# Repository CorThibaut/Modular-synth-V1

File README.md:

# Modular-synth-V1
Personal project focused on building multiple analog synthesizer modules for the Eurorack format.

## Gallery

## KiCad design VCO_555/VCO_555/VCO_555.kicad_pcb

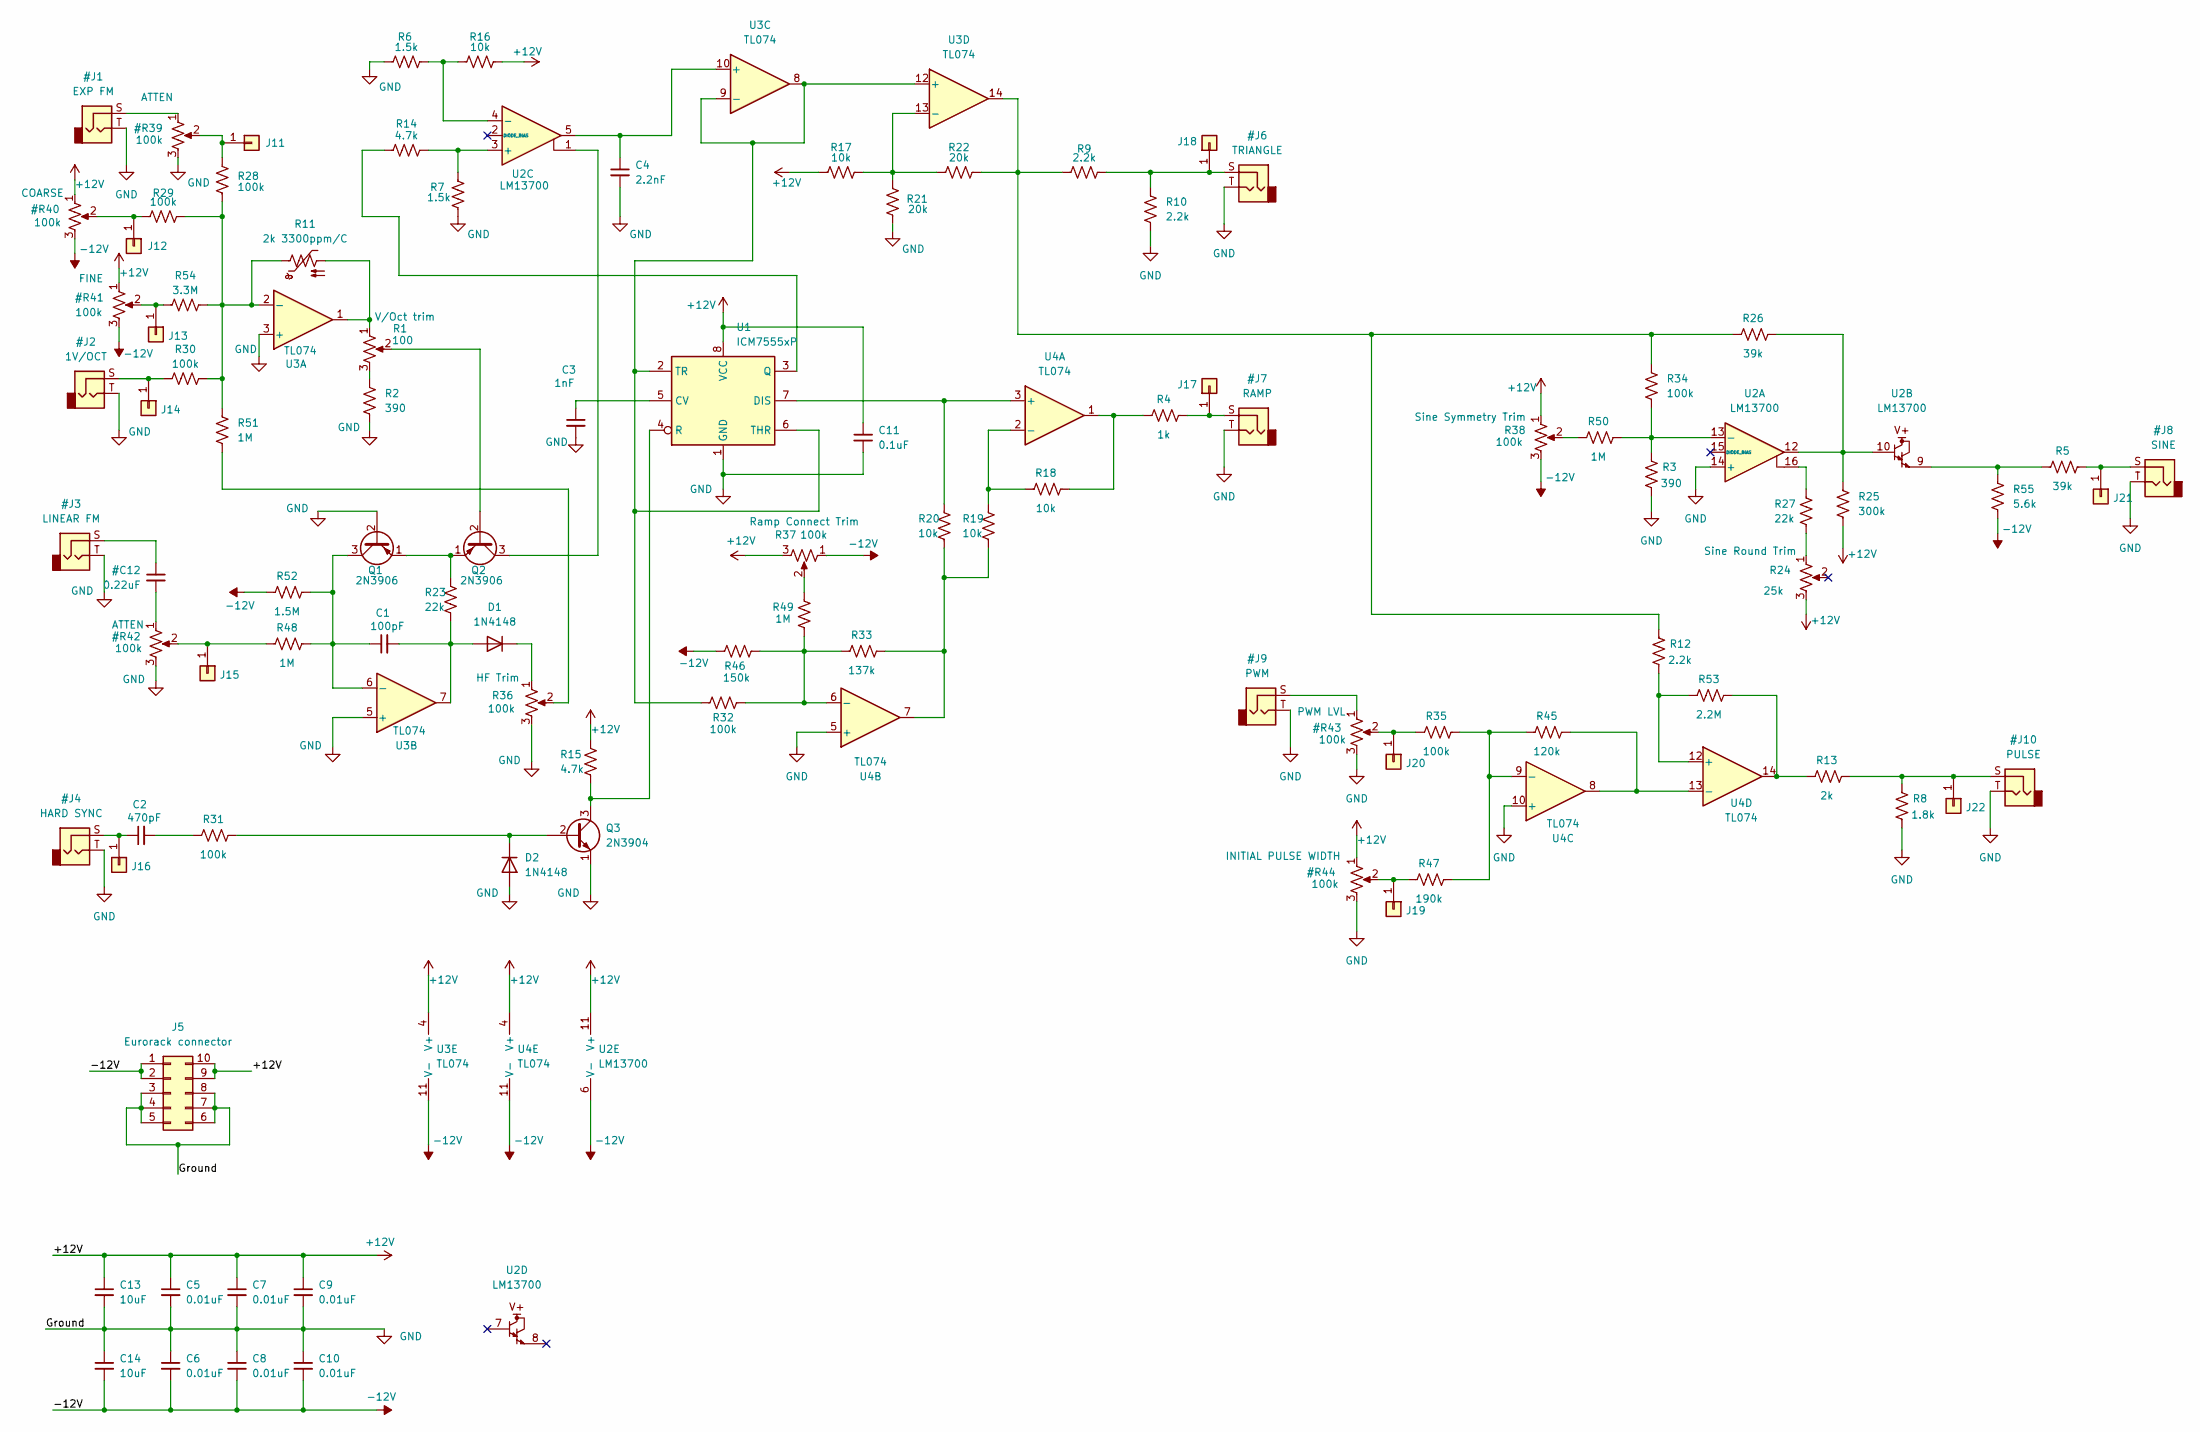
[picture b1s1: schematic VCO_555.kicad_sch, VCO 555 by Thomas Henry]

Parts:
C1: 100pF; C_Axial_L3.8mm_D2.6mm_P7.50mm_Horizontal
C2: 470pF; C_Disc_D7.5mm_W2.5mm_P5.00mm
C3: 1nF; C_Disc_D4.7mm_W2.5mm_P5.00mm
C4: 2.2nF; C_Disc_D5.1mm_W3.2mm_P5.00mm
C5, C6, C7, C8, C9, C10: 0.01uF; C_Disc_D5.0mm_W2.5mm_P5.00mm
C11: 0.1uF; C_Rect_L4.6mm_W3.0mm_P2.50mm_MKS02_FKP02
C13, C14: 10uF; CP_Radial_Tantal_D10.5mm_P5.00mm
D1, D2: 1N4148; D_DO-35_SOD27_P7.62mm_Horizontal
J5: Eurorack connector; IDC-Header_2x05_P2.54mm_Vertical
J11: EXP FM; Pin_D0.7mm_L6.5mm_W1.8mm_FlatFork
J12: COARSE; Pin_D0.7mm_L6.5mm_W1.8mm_FlatFork
J13: FINE; Pin_D0.7mm_L6.5mm_W1.8mm_FlatFork
J14: 1V/OCT; Pin_D0.7mm_L6.5mm_W1.8mm_FlatFork
J15: Linear FM; Pin_D0.7mm_L6.5mm_W1.8mm_FlatFork
J16: HardSync; Pin_D0.7mm_L6.5mm_W1.8mm_FlatFork
J17: Conn_01x01; Pin_D0.7mm_L6.5mm_W1.8mm_FlatFork
J18: Triangle; Pin_D0.7mm_L6.5mm_W1.8mm_FlatFork
J19: INIT PW; Pin_D0.7mm_L6.5mm_W1.8mm_FlatFork
J20: PWM; Pin_D0.7mm_L6.5mm_W1.8mm_FlatFork
J21: Sine; Pin_D0.7mm_L6.5mm_W1.8mm_FlatFork
J22: Pulse; Pin_D0.7mm_L6.5mm_W1.8mm_FlatFork
Q1, Q2: 2N3906; TO-92_Inline
Q3: 2N3904; TO-92_Inline
R1: 100; Potentiometer_Bourns_3386X_Horizontal
R2, R3: 390; R_Axial_DIN0207_L6.3mm_D2.5mm_P10.16mm_Horizontal
R4: 1k; R_Axial_DIN0207_L6.3mm_D2.5mm_P10.16mm_Horizontal
R5, R26: 39k; R_Axial_DIN0207_L6.3mm_D2.5mm_P10.16mm_Horizontal
R6, R7: 1.5k; R_Axial_DIN0207_L6.3mm_D2.5mm_P10.16mm_Horizontal
R8: 1.8k; R_Axial_DIN0207_L6.3mm_D2.5mm_P10.16mm_Horizontal
R9, R10, R12: 2.2k; R_Axial_DIN0207_L6.3mm_D2.5mm_P10.16mm_Horizontal
R11: 2k 3300ppm/C; R_Axial_DIN0207_L6.3mm_D2.5mm_P7.62mm_Horizontal
R13: 2k; R_Axial_DIN0207_L6.3mm_D2.5mm_P10.16mm_Horizontal
R14, R15: 4.7k; R_Axial_DIN0207_L6.3mm_D2.5mm_P10.16mm_Horizontal
R16, R17, R18, R19, R20: 10k; R_Axial_DIN0207_L6.3mm_D2.5mm_P10.16mm_Horizontal
R21, R22: 20k; R_Axial_DIN0207_L6.3mm_D2.5mm_P10.16mm_Horizontal
R23, R27: 22k; R_Axial_DIN0207_L6.3mm_D2.5mm_P10.16mm_Horizontal
R24: 25k; Potentiometer_Bourns_3296W_Vertical
R25: 300k; R_Axial_DIN0207_L6.3mm_D2.5mm_P10.16mm_Horizontal
R28, R29, R30, R31, R32, R34, R35: 100k; R_Axial_DIN0207_L6.3mm_D2.5mm_P10.16mm_Horizontal
R33: 137k; R_Axial_DIN0207_L6.3mm_D2.5mm_P10.16mm_Horizontal
R36: 100k; Potentiometer_Piher_PT-6-V_Vertical
R37: 100k; Potentiometer_Bourns_3296W_Vertical
R38: 100k; Potentiometer_Bourns_3296Y_Vertical
R45: 120k; R_Axial_DIN0207_L6.3mm_D2.5mm_P10.16mm_Horizontal
R46: 150k; R_Axial_DIN0207_L6.3mm_D2.5mm_P10.16mm_Horizontal
R47: 190k; R_Axial_DIN0207_L6.3mm_D2.5mm_P10.16mm_Horizontal
R48, R49, R50, R51: 1M; R_Axial_DIN0207_L6.3mm_D2.5mm_P10.16mm_Horizontal
R52: 1.5M; R_Axial_DIN0207_L6.3mm_D2.5mm_P10.16mm_Horizontal
R53: 2.2M; R_Axial_DIN0207_L6.3mm_D2.5mm_P10.16mm_Horizontal
R54: 3.3M; R_Axial_DIN0207_L6.3mm_D2.5mm_P10.16mm_Horizontal
R55: 5.6k; R_Axial_DIN0207_L6.3mm_D2.5mm_P10.16mm_Horizontal
U1: ICM7555xP; CERDIP-8_W7.62mm_SideBrazed_Socket
U2: LM13700; CERDIP-16_W7.62mm_SideBrazed_Socket
U3, U4: TL074; CERDIP-14_W7.62mm_SideBrazed_Socket

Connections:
unnamed: C2.2, R31.1
unnamed: C1.2, D1.2 (A), R23.2, U3.7
unnamed: D1.1 (K), R36.1
unnamed: D2.1 (K), Q3.2 (B), R31.2
unnamed: C1.1, Q1.3 (C), R48.2, R52.2, U3.6 (-)
unnamed: Q1.1 (E), Q2.1 (E), R23.1
unnamed: Q2.2 (B), R1.2
unnamed: Q2.3 (C), U2.1
unnamed: Q3.3 (C), R15.2, U1.4 (R)
unnamed: R1.1, R11.2, U3.1
unnamed: R1.3, R2.1
unnamed: R5.1, R55.1, U2.9
unnamed: R9.1, R12.1, R22.2, R26.1, R34.1, U3.14
unnamed: R13.1, R53.2, U4.14
unnamed: R4.1, R18.2, U4.1
unnamed: R19.2, R20.2, R33.2, U4.7
unnamed: R24.1, R27.2
unnamed: R25.1, R26.2, U2.10, U2.12
unnamed: R27.1, U2.16
unnamed: R36.2, R51.2
unnamed: R37.2, R49.1
unnamed: R38.2, R50.1
unnamed: C3.1, U1.5 (CV)
unnamed: R20.1, U1.7 (DIS), U4.3 (+)
unnamed: R14.1, U1.3 (Q)
unnamed: R32.1, U1.2 (TR), U1.6 (THR), U3.8, U3.9 (-), U3.12 (+)
unnamed: R3.1, R34.2, R50.2, U2.13 (-)
unnamed: R7.2, R14.2, U2.3 (+)
unnamed: R6.2, R16.1, U2.4 (-)
unnamed: R11.1, R28.2, R29.2, R30.2, R51.1, R54.2, U3.2 (-)
unnamed: C4.1, U2.5, U3.10 (+)
unnamed: R17.2, R21.1, R22.1, U3.13 (-)
unnamed: R18.1, R19.1, U4.2 (-)
unnamed: R32.2, R33.1, R46.2, R49.2, U4.6 (-)
unnamed: R35.2, R45.1, R47.2, U4.9 (-)
unnamed: R12.2, R53.1, U4.12 (+)
unnamed: R45.2, U4.8, U4.13 (-)

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
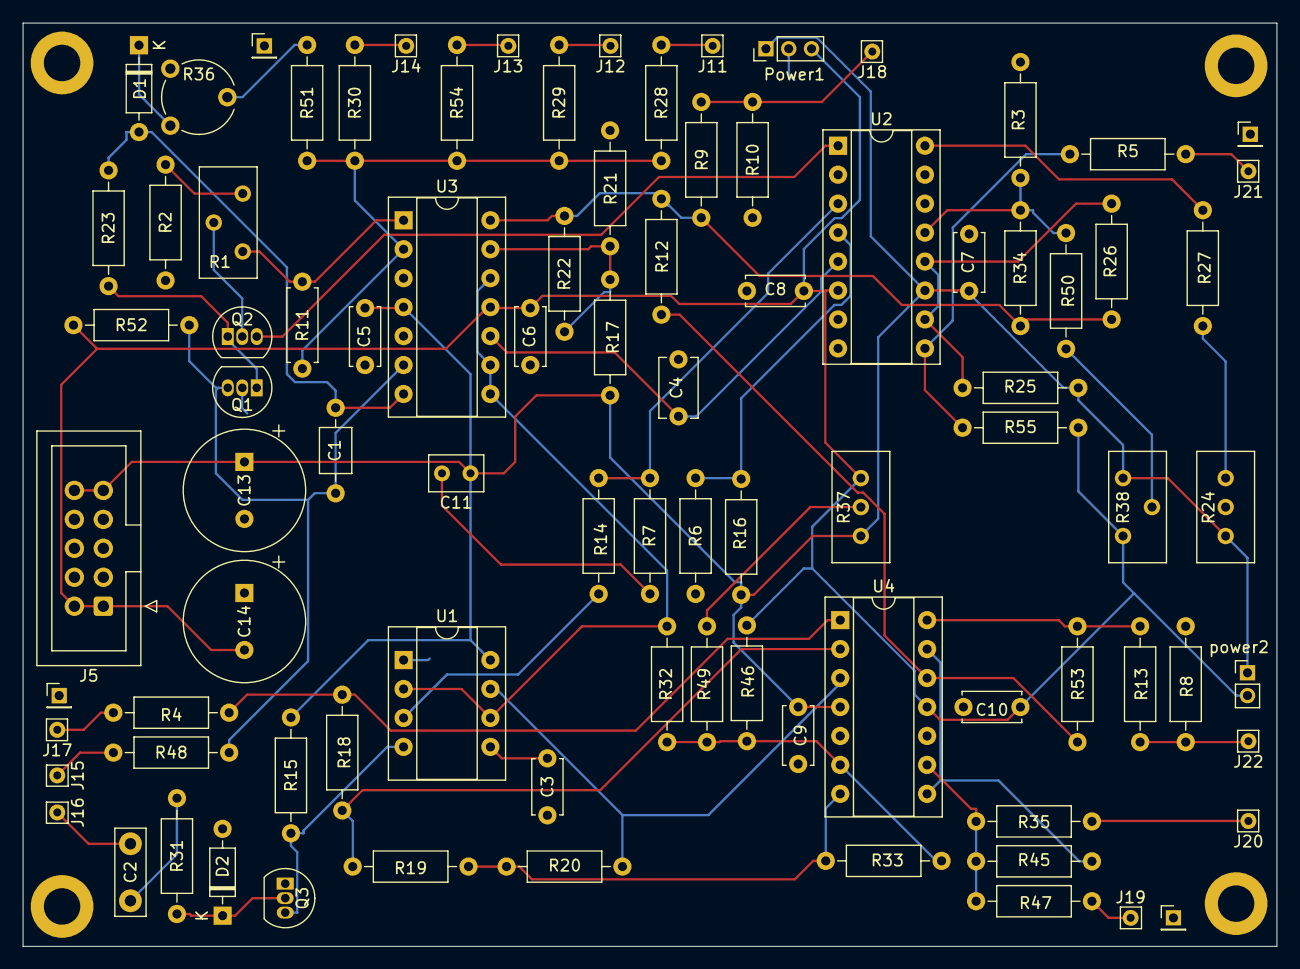
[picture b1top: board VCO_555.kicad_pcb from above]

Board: 2 copper layers, 110.0 x 81.0 mm, 94 parts (0 on the bottom side), 52 nets.

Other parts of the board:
GND1, GND2, GND3, GND4: PinHeader_1x01_P2.00mm_Vertical
MH1, MH2, MH3, MH4: MountingHole_3.2mm_M3_ISO14580_Pad
Power1: PinHeader_1x03_P2.00mm_Vertical
power2: PinHeader_1x02_P2.00mm_Vertical

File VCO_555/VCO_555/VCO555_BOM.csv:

"Reference","Value","Datasheet","Footprint","Qty","DNP"
"C1","100pF","~","","1",""
"C2","470pF","~","","1",""
"C3","0.001uF","~","","1",""
"C4","2200pF","~","","1",""
"C5,C6,C7,C8,C9,C10","0.01uF","~","","6",""
"C11","0.1uF","~","","1",""
"C12","0.22uF","~","","1",""
"C13,C14","10uF","~","","2",""
"D1,D2","1N4148","https://assets.nexperia.com/documents/data-sheet/1N4148_1N4448.pdf","Diode_THT:D_DO-35_SOD27_P7.62mm_Horizontal","2",""
"J1","EXP FM","~","Connector_Audio:Jack_3.5mm_CUI_SJ1-3523N_Horizontal","1",""
"J2","1V/OCT","~","Connector_Audio:Jack_3.5mm_CUI_SJ1-3523N_Horizontal","1",""
"J3","LINEAR FM","~","Connector_Audio:Jack_3.5mm_CUI_SJ1-3523N_Horizontal","1",""
"J4","HARD SYNC","~","Connector_Audio:Jack_3.5mm_CUI_SJ1-3523N_Horizontal","1",""
"J5","Eurorack connector","~","Connector_Harwin:Harwin_Gecko-G125-MVX1605L0X_2x08_P1.25mm_Vertical","1",""
"J6","TRIANGLE","~","Connector_Audio:Jack_3.5mm_CUI_SJ1-3523N_Horizontal","1",""
"J7","RAMP","~","Connector_Audio:Jack_3.5mm_CUI_SJ1-3523N_Horizontal","1",""
"J8","SINE","~","Connector_Audio:Jack_3.5mm_CUI_SJ1-3523N_Horizontal","1",""
"J9","PWM","~","Connector_Audio:Jack_3.5mm_CUI_SJ1-3523N_Horizontal","1",""
"J10","PULSE","~","Connector_Audio:Jack_3.5mm_CUI_SJ1-3523N_Horizontal","1",""
"Q1,Q2","2N3906","https://www.onsemi.com/pub/Collateral/2N3906-D.PDF","Package_TO_SOT_THT:TO-92_Inline","2",""
"Q3","2N3904","https://www.onsemi.com/pub/Collateral/2N3903-D.PDF","Package_TO_SOT_THT:TO-92_Inline","1",""
"R1","100","~","Potentiometer_SMD:Potentiometer_ACP_CA6-VSMD_Vertical","1",""
"R2,R3","390","~","Resistor_THT:R_Axial_DIN0207_L6.3mm_D2.5mm_P10.16mm_Horizontal","2",""
"R4","1k","~","Resistor_THT:R_Axial_DIN0207_L6.3mm_D2.5mm_P10.16mm_Horizontal","1",""
"R5,R26","39k","~","Resistor_THT:R_Axial_DIN0207_L6.3mm_D2.5mm_P10.16mm_Horizontal","2",""
"R6,R7","1.5k","~","Resistor_THT:R_Axial_DIN0207_L6.3mm_D2.5mm_P10.16mm_Horizontal","2",""
"R8","1.8k","~","Resistor_THT:R_Axial_DIN0207_L6.3mm_D2.5mm_P10.16mm_Horizontal","1",""
"R9,R10,R12","2.2k","~","Resistor_THT:R_Axial_DIN0207_L6.3mm_D2.5mm_P10.16mm_Horizontal","3",""
"R11","2k 3300ppm/C","~","Resistor_THT:R_Axial_DIN0207_L6.3mm_D2.5mm_P7.62mm_Horizontal","1",""
"R13","2k","~","Resistor_THT:R_Axial_DIN0207_L6.3mm_D2.5mm_P10.16mm_Horizontal","1",""
"R14,R15","4.7k","~","Resistor_THT:R_Axial_DIN0207_L6.3mm_D2.5mm_P10.16mm_Horizontal","2",""
"R16,R17,R18,R19,R20","10k","~","Resistor_THT:R_Axial_DIN0207_L6.3mm_D2.5mm_P10.16mm_Horizontal","5",""
"R21,R22","20k","~","Resistor_THT:R_Axial_DIN0207_L6.3mm_D2.5mm_P10.16mm_Horizontal","2",""
"R23,R27","22k","~","Resistor_THT:R_Axial_DIN0207_L6.3mm_D2.5mm_P10.16mm_Horizontal","2",""
"R24","25k","~","Potentiometer_SMD:Potentiometer_ACP_CA6-VSMD_Vertical","1",""
"R25","300k","~","Resistor_THT:R_Axial_DIN0207_L6.3mm_D2.5mm_P10.16mm_Horizontal","1",""
"R28,R29,R30,R31,R32,R34,R35,R36,R37,R38,R39,R40,R41,R42,R43,R44","100k","~","-- mixed values --","16",""
"R33","137k","~","Resistor_THT:R_Axial_DIN0207_L6.3mm_D2.5mm_P10.16mm_Horizontal","1",""
"R45,R53","120k","~","Resistor_THT:R_Axial_DIN0207_L6.3mm_D2.5mm_P10.16mm_Horizontal","2",""
"R46","150k","~","Resistor_THT:R_Axial_DIN0207_L6.3mm_D2.5mm_P10.16mm_Horizontal","1",""
"R47","330k","~","Resistor_THT:R_Axial_DIN0207_L6.3mm_D2.5mm_P10.16mm_Horizontal","1",""
"R48,R49,R50,R51","1M","~","Resistor_THT:R_Axial_DIN0207_L6.3mm_D2.5mm_P10.16mm_Horizontal","4",""
"R52","1.5M","~","Resistor_THT:R_Axial_DIN0207_L6.3mm_D2.5mm_P10.16mm_Horizontal","1",""
"R54","3.3M","~","Resistor_THT:R_Axial_DIN0207_L6.3mm_D2.5mm_P10.16mm_Horizontal","1",""
"R55","5.6k","~","Resistor_THT:R_Axial_DIN0207_L6.3mm_D2.5mm_P10.16mm_Horizontal","1",""
"U1","ICM7555xP","http://www.intersil.com/content/dam/Intersil/documents/icm7/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","Package_DIP:DIP-8_W7.62mm","1",""
"U2","LM13700","http://www.ti.com/lit/ds/symlink/lm13700.pdf","","1",""
"U3,U4","TL074","http://www.ti.com/lit/ds/symlink/tl071.pdf","","2",""

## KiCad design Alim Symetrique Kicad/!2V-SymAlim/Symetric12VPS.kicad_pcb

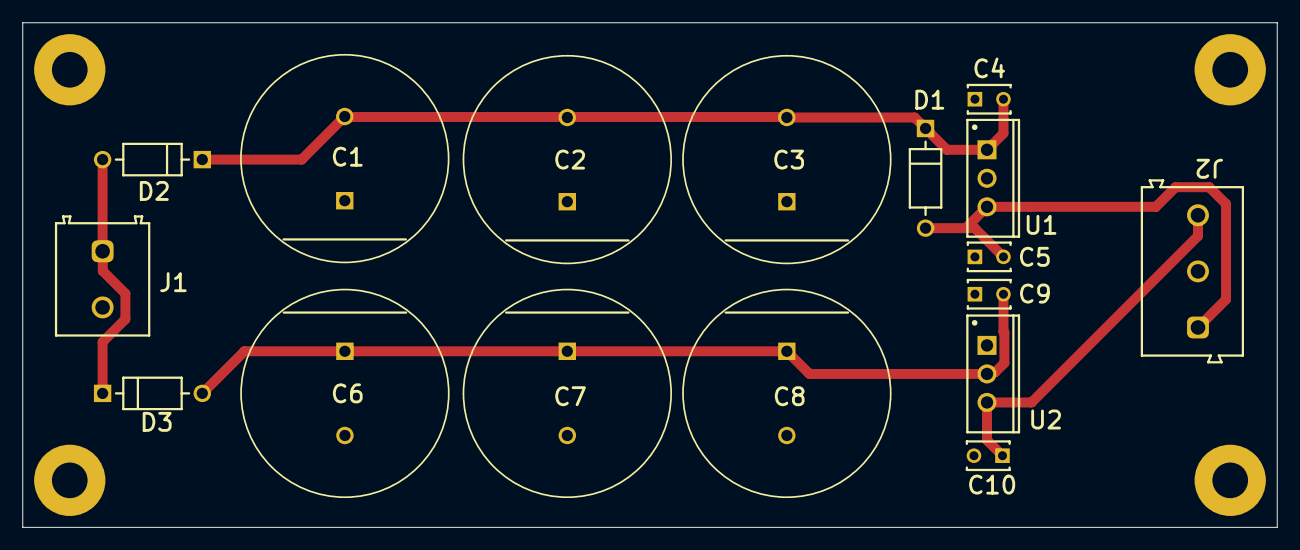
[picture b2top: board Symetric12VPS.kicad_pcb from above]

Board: 2 copper layers, 111.8 x 45.0 mm, 17 parts (0 on the bottom side), 6 nets.

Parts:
C1, C2, C3, C6, C7, C8: EEUFK1E472S; FP-RAD-TH-D_18_0_5-L_25_2-MFG
C4, C5, C9, C10: C315C100J2G5TA; KEMT-C315-THT-2
D1, D2, D3: 1N4007; FP-1N4007-MFG
J1: 691213710002
J2: 691101710003
U1: L7812CV; TO220
U2: L7912CV; TO-220

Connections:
GND: C1.1, C2.1, C3.1, C4.1, C5.1, C6.2, C7.2, C8.2, C9.1, C10.2, J1.2, J2.2, U1.2, U2.1
NetC1_2: C1.2, C2.2, C3.2, C4.2, D1.1, D2.1, U1.1
NetC5_2: C5.2, D1.2, J2.1, U1.3
NetC6_1: C6.1, C7.1, C8.1, C9.2, D3.2, U2.2
NetC10_1: C10.1, J2.3, U2.3
NetD2_2: D2.2, D3.1, J1.1

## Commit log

2026-04-01 Init
    first commit
2026-04-02 Second
    added gitignore
2026-04-02 image
    added image
2026-04-12 New Module
